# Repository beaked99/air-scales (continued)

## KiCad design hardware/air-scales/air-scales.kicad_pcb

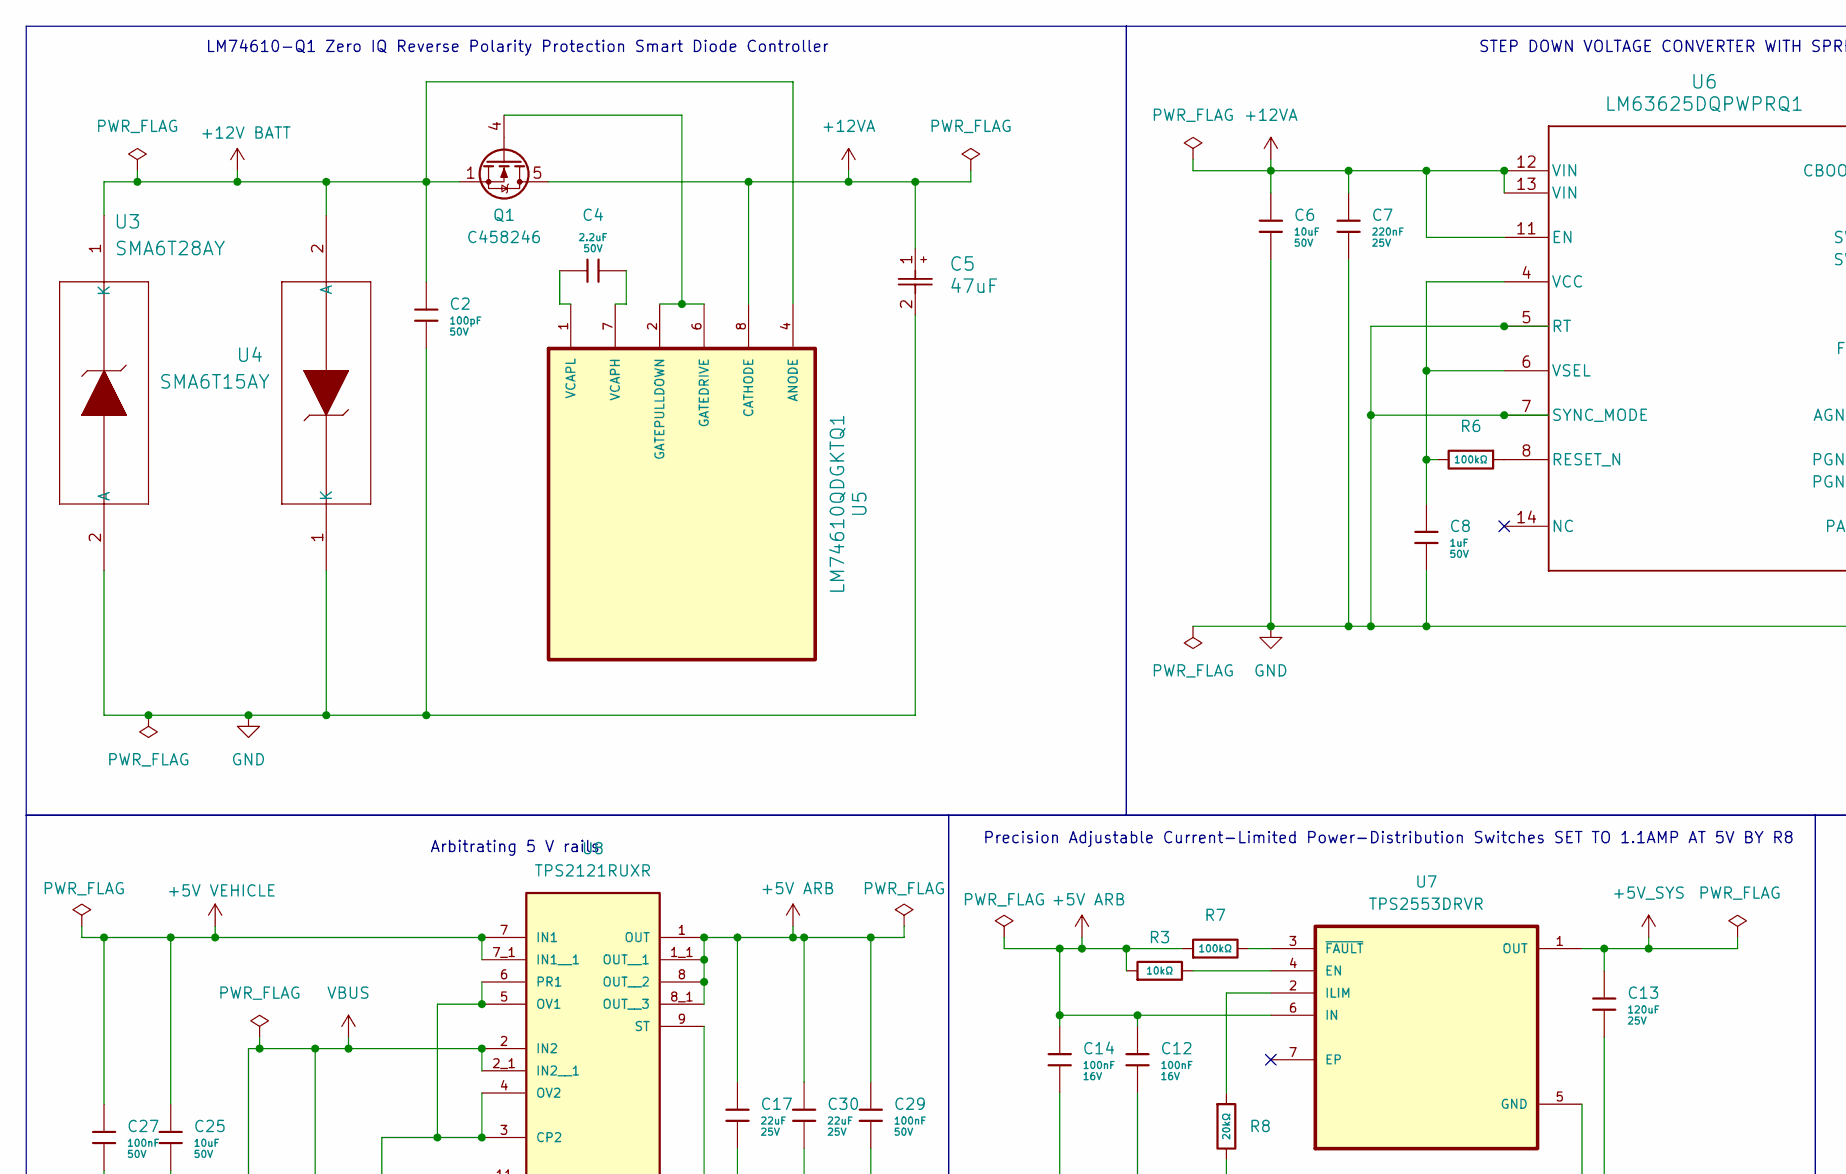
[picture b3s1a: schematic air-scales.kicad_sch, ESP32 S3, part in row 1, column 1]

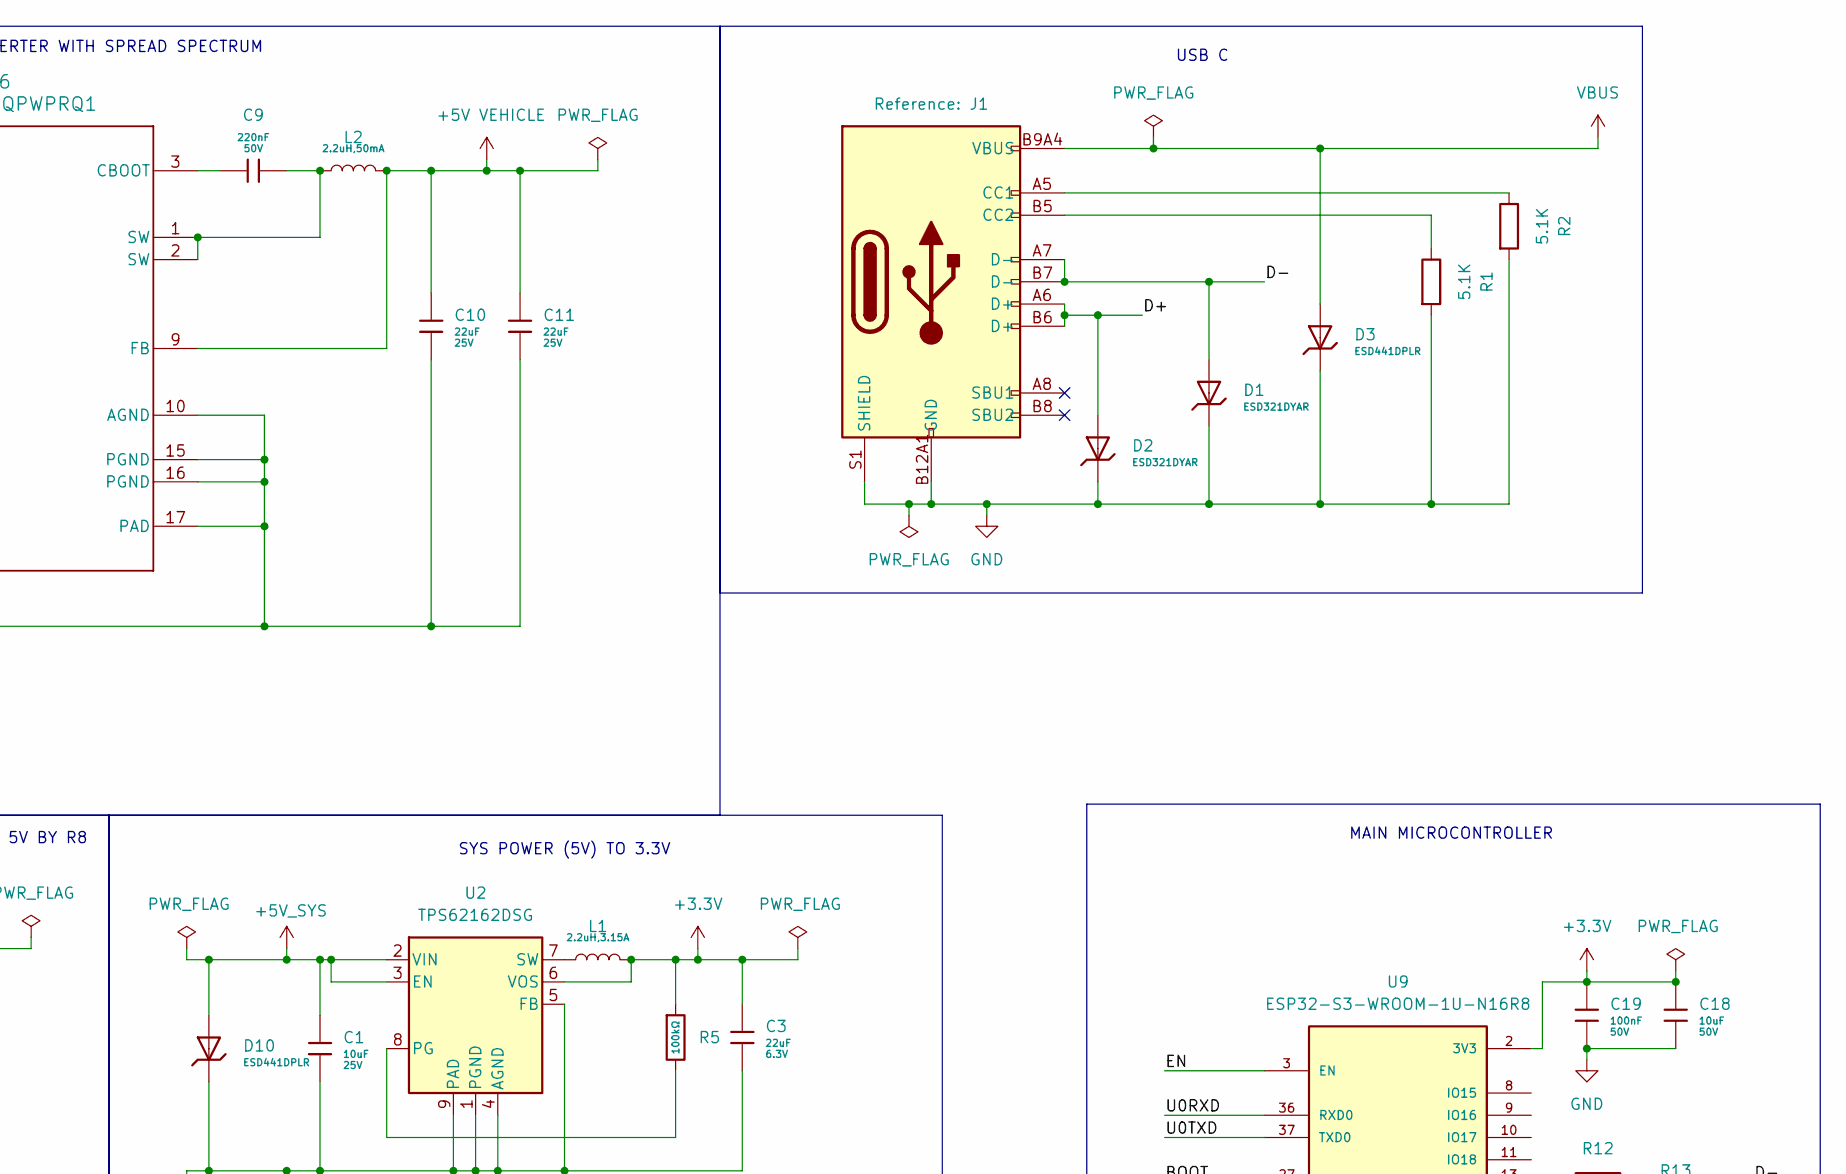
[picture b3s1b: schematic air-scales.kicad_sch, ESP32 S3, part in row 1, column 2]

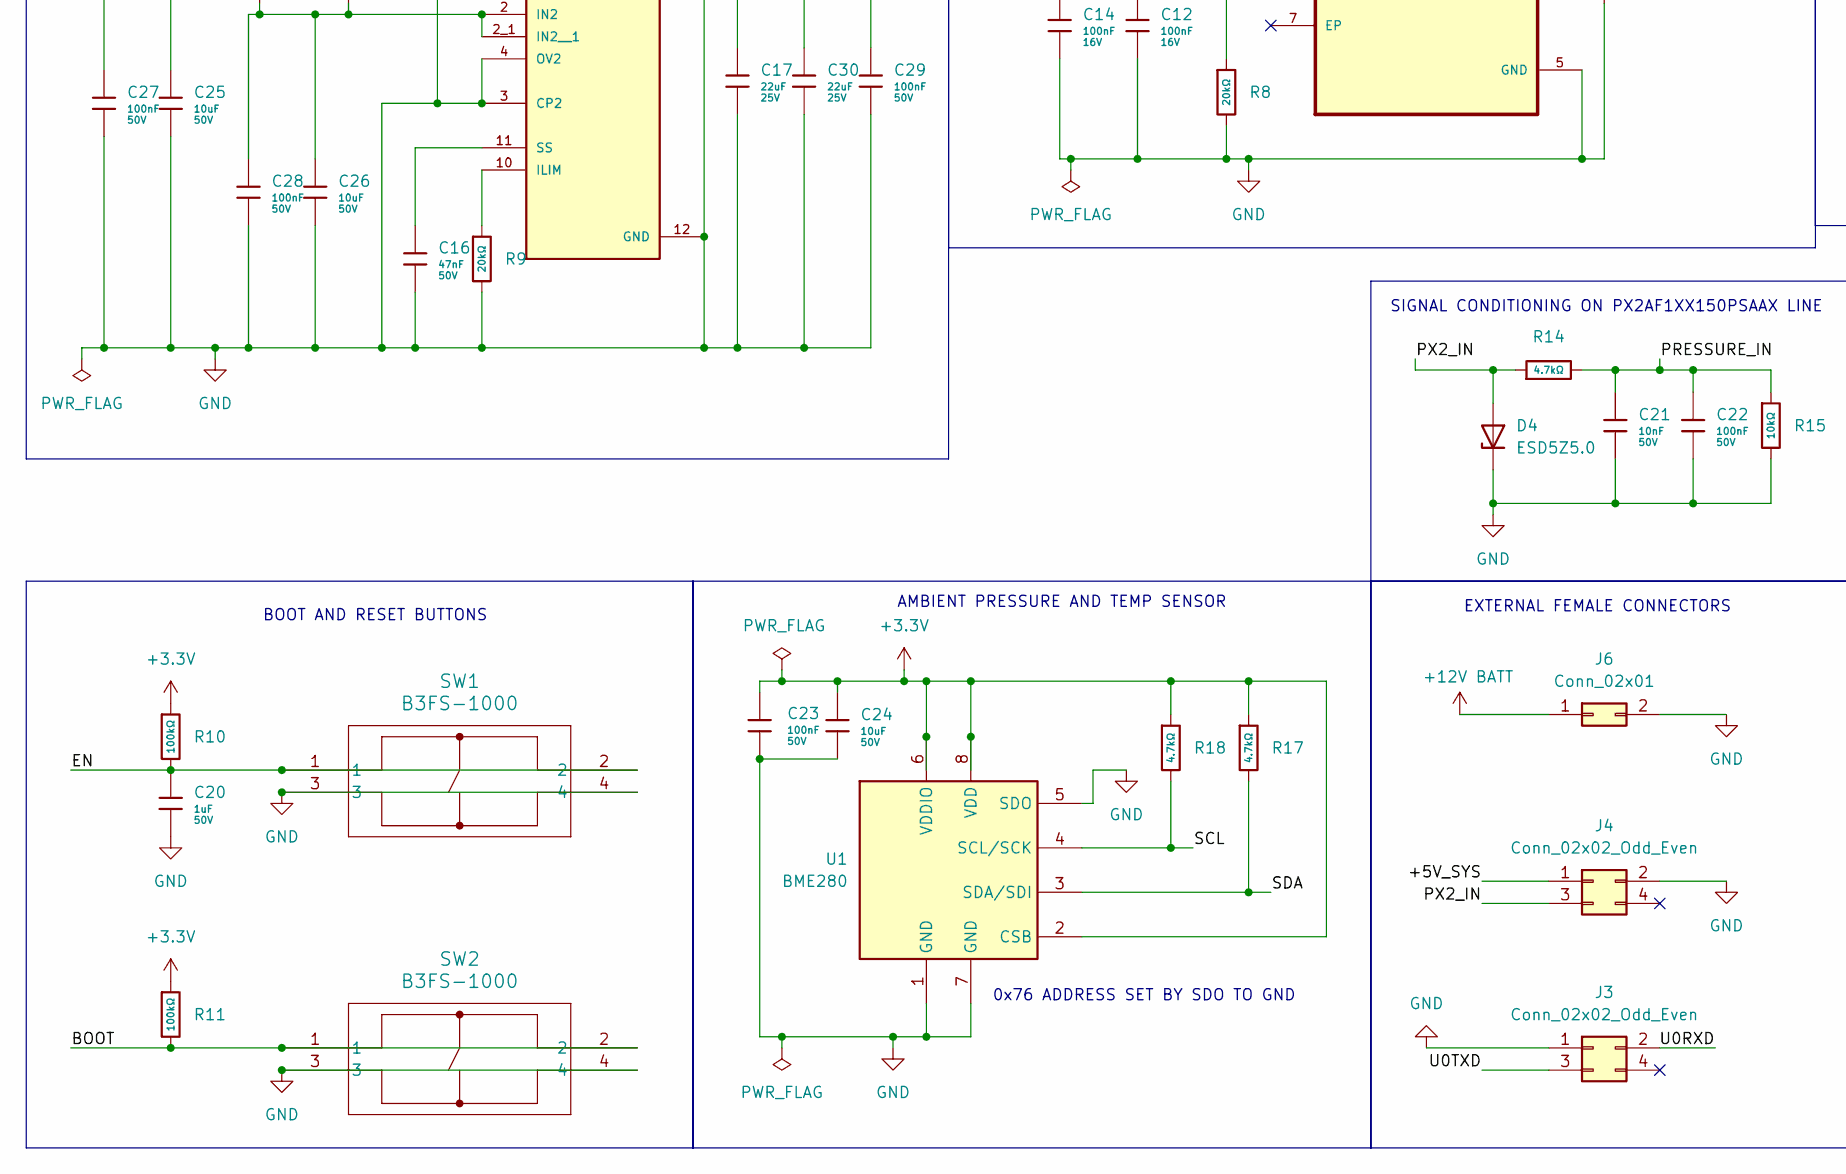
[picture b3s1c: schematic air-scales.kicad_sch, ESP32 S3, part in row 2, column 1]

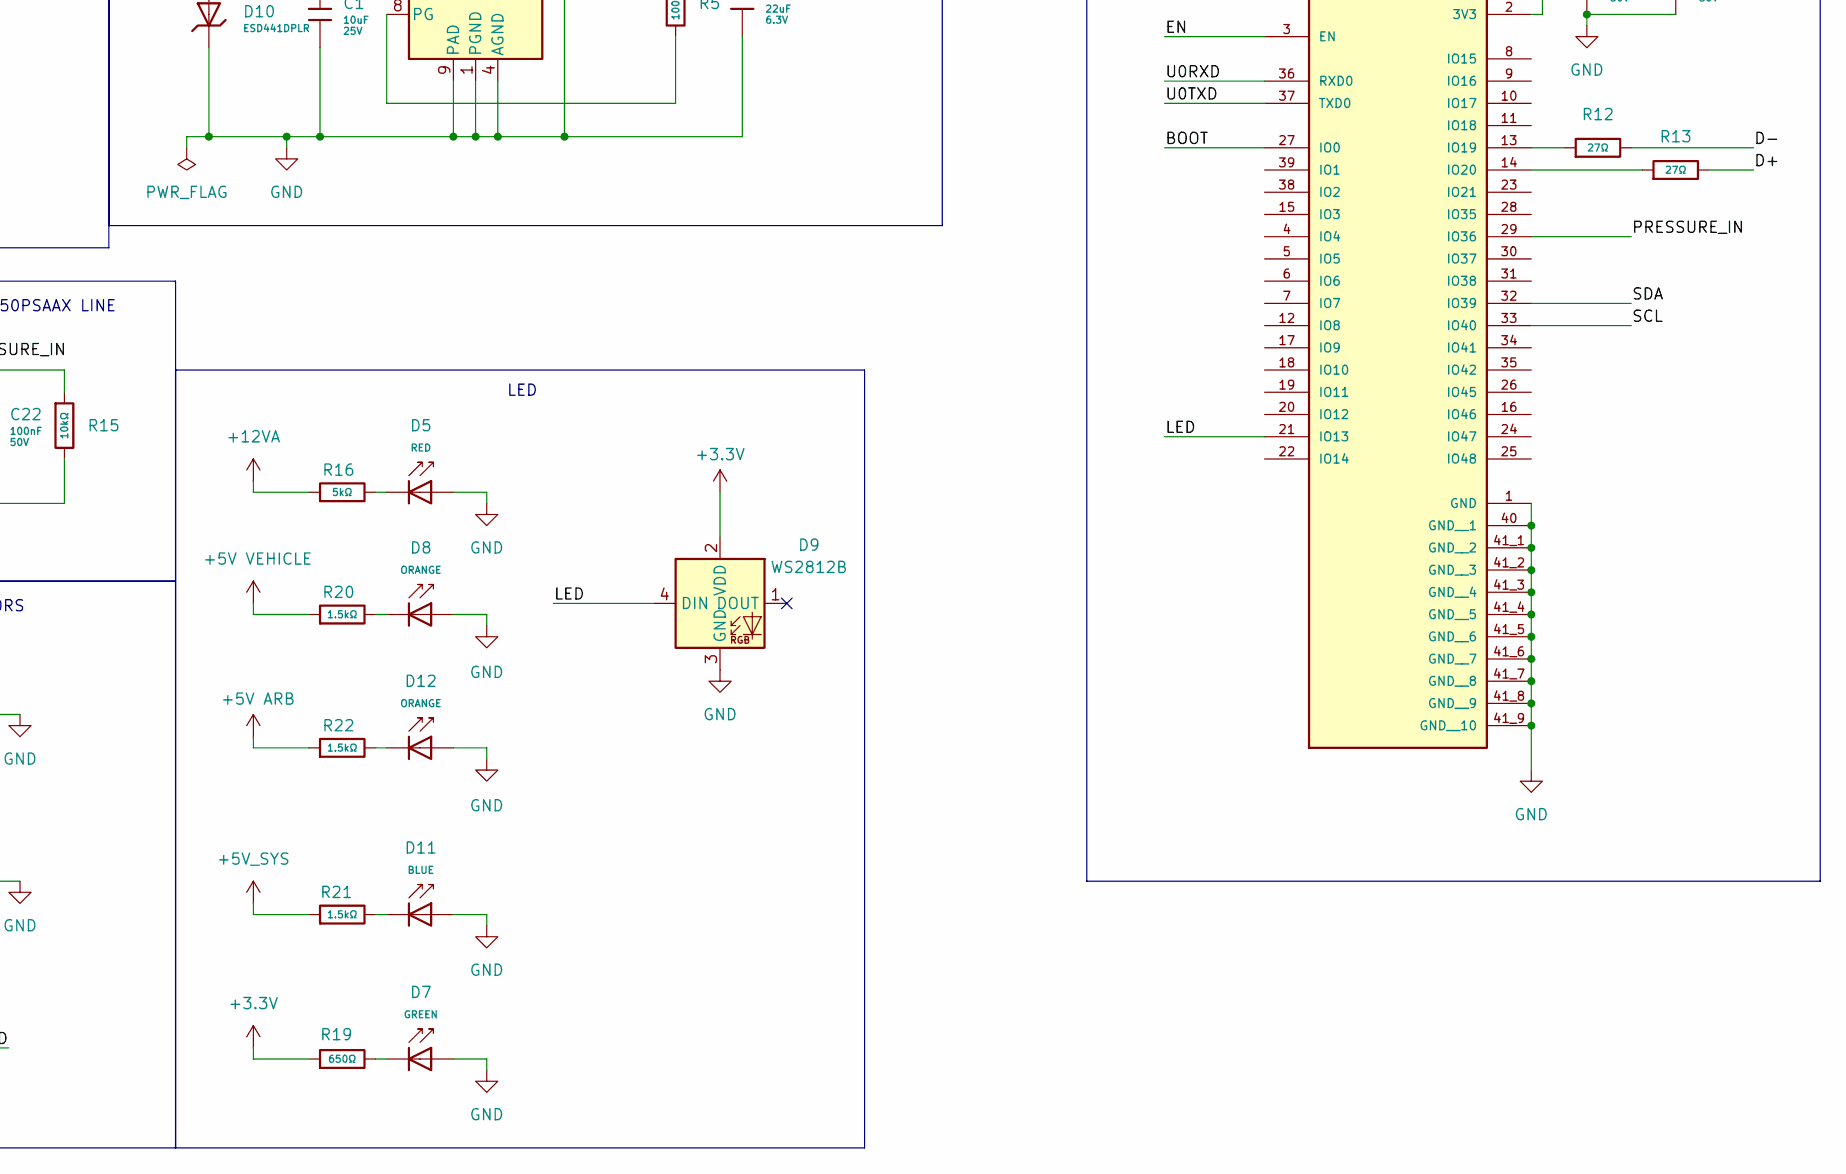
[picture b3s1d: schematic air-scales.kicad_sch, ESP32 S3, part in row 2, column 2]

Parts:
C1: 10uF; C_0603; Voltage Rated 25V; Tolerance ±20%; Part CL10A106MA8NRNC; LCSC C96446
C2: 100pF; C_0402; Voltage Rated 50V; Tolerance ±5%; Part 0402CG101J500NT; LCSC C1546
C3: 22uF; C_0603; Voltage Rated 6.3V; Tolerance ±20%; Part CL10A226MQ8NRNC; LCSC C59461
C4: 2.2uF; C_1206; Voltage Rated 50V; Tolerance ±10%; Part CL31B225KBHNNNE; LCSC C50254
C5: 47uF; CAP_PC_10X12P7_NCH
C6, C18, C24, C25, C26: 10uF; C_1206; Voltage Rated 50V; Tolerance ±10%; Part CL31A106KBHNNNE; LCSC C13585
C7: 220nF; C_0603; Voltage Rated 25V; Tolerance ±10%; Part CL10B224KA8NNNC; LCSC C21120
C8: 1uF; C_1206; Voltage Rated 50V; Tolerance ±10%; Part CL31B105KBHNNNE; LCSC C1848
C9: 220nF; C_1206; Voltage Rated 50V; Tolerance ±10%; Part 1206B224K500NT; LCSC C1857
C10, C11, C17, C30: 22uF; C_1206; Voltage Rated 25V; Tolerance ±10%; Part CL31A226KAHNNNE; LCSC C12891
C12, C14: 100nF; C_0402; Voltage Rated 16V; Tolerance ±10%; Part CL05B104KO5NNNC; LCSC C1525
C13: 120uF; C_0603; Voltage Rated 25V; Tolerance ±20%; Part CL10A106MA8NRNC; LCSC C96446
C16: 47nF; C_0603; Voltage Rated 50V; Tolerance ±10%; Part CL10B473KB8NNNC; LCSC C1622
C19, C22, C23, C27, C28, C29: 100nF; C_0603; Voltage Rated 50V; Tolerance ±10%; Part CC0603KRX7R9BB104; LCSC C14663
C20: 1uF; C_0603; Voltage Rated 50V; Tolerance ±10%; Part CL10A105KB8NNNC; LCSC C15849
C21: 10nF; C_0603; Voltage Rated 50V; Tolerance ±10%; Part 0603B103K500NT; LCSC C57112
D1, D2: ESD321DYAR; D_SOD-523; Part H5VND5BA; LCSC C42413899
D3, D10: ESD441DPLR; D_SOD-123FL; Part SMF20A; LCSC C41411782
D4: ESD5Z5.0; D_SOD-523
D5: RED; D_0603; Part KT-0603R; LCSC C2286
D7: GREEN; D_0603; Part KT-0603R; LCSC C2286
D8, D12: ORANGE; D_0603; Part KT-0603R; LCSC C2286
D9: WS2812B; LED-SMD_4P-L1.6-W1.5_XL-1615RGBC-WS2812B; LCSC C5349954
D11: BLUE; D_0603; Part KT-0603R; LCSC C2286
J1: Connector, USB-TYPE-C-16P; TYPE-C-SMD_HX-TYPE-C-16PIN; LCSC C2927039
J3, J4: Conn_02x02_Odd_Even; Molex_Micro-Fit_3.0_43045-0418_2x02-1MP_P3.00mm_Vertical
J6: Conn_02x01; Molex_Micro-Fit_3.0_43045-0218_2x01-1MP_P3.00mm_Vertical
L1: 2.2uH,3.15A; L_0805; Tolerance ±10%; Part CMI201209U2R2KT; LCSC C1043
L2: 2.2uH,50mA; L_0805; Tolerance ±10%; Part CMI201209U2R2KT; LCSC C1043
Q1: C458246; LFPAK56
R1, R2: 5.1K; R_0603
R3, R15: 10kΩ; R_0603; Overload Voltage (Max) 75V; Tolerance ±1%; Part 0603WAF1002T5E; LCSC C25804
R5, R6, R7, R10, R11: 100kΩ; R_0603; Overload Voltage (Max) 75V; Tolerance ±1%; Part 0603WAF1003T5E; LCSC C25803
R8, R9: 20kΩ; R_0402; Overload Voltage (Max) 50V; Tolerance ±1%; Part 0402WGF2002TCE; LCSC C25765
R12, R13: 27Ω; R_0603; Overload Voltage (Max) 75V; Tolerance ±1%; Part 0603WAF270JT5E; LCSC C25190
R14, R17, R18: 4.7kΩ; R_0603; Overload Voltage (Max) 75V; Tolerance ±1%; Part 0603WAF4701T5E; LCSC C23162
R16: 5kΩ; R_0603; Overload Voltage (Max) 75V; Tolerance ±1%; Part 0603WAF1002T5E
R19: 650Ω; R_0603; Overload Voltage (Max) 75V; Tolerance ±1%; Part 0603WAF3301T5E
R20, R21, R22: 1.5kΩ; R_0603; Overload Voltage (Max) 75V; Tolerance ±1%; Part 0603WAF3301T5E
SW1, SW2: B3FS-1000; SW_B3FS-1000_OMR
U1: BME280; Bosch_LGA-8_2.5x2.5mm_P0.65mm_ClockwisePinNumbering; LCSC C92489
U2: TPS62162DSG; WSON-8-1EP_2x2mm_P0.5mm_EP0.9x1.6mm_ThermalVias
U3: SMA6T28AY; SMA_UNI_STM
U4: SMA6T15AY; SMA_UNI_STM
U5: LM74610QDGKTQ1; SOP65P490X110-8N
U6: LM63625DQPWPRQ1; PWP0016K_N
U7: TPS2553DRVR; SON65P200X200X80-7N
U8: TPS2121RUXR; IC_TPS2121RUXR
U9: ESP32-S3-WROOM-1U-N16R8; XCVR_ESP32-S3-WROOM-1U-N16R8; PARTREV v1.1; LCSC C3013946

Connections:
+3.3V: C3.1, C18.1, C19.1, C23.1, C24.1, D9.2 (VDD), L1.2, R5.1, R10.1, R11.1, R17.1, R18.1, R19.1, U1.2 (CSB), U1.6 (VDDIO), U1.8 (VDD), U2.6 (VOS), U9.2 (3V3)
+5V ARB: C12.1, C14.1, C17.1, C29.1, C30.1, R3.1, R7.1, R22.1, U7.6 (IN), U8.1 (OUT), U8.1_1 (OUT__1), U8.8 (OUT__2), U8.8_1 (OUT__3)
+5V VEHICLE: C10.1, C11.1, C25.1, C27.1, L2.2, R20.1, U6.9 (FB), U8.7 (IN1), U8.7_1 (IN1__1)
+5V_SYS: C1.1, C13.1, D10.2, J4.1, R21.1, U2.2 (VIN), U2.3 (EN), U7.1 (OUT)
+12V BATT: C2.1, J6.1, Q1.1 (S), Q1.2 (S), Q1.3 (S), U3.1 (K), U4.2 (A), U5.4 (ANODE)
+12VA: C5.1, C6.1, C7.1, Q1.5 (D), R16.1, U5.8 (CATHODE), U6.11 (EN), U6.12 (VIN), U6.13 (VIN)
/BOOT: R11.2, SW2.1, SW2.2, U9.27 (IO0)
/D+: D2.2, J1.A6 (D+), J1.B6 (D+), R13.2
/D-: D1.2, J1.A7 (D-), J1.B7 (D-), R12.2
/EN: C20.1, R10.2, SW1.1, SW1.2, U9.3 (EN)
/LED: D9.4 (DIN), U9.21 (IO13)
/PRESSURE_IN: C21.1, C22.1, R14.2, R15.1, U9.29 (IO36)
/PX2_IN: D4.2 (A), J4.3, R14.1
/SCL: R18.2, U1.4 (SCL/SCK), U9.33 (IO40)
/SDA: R17.2, U1.3 (SDA/SDI), U9.32 (IO39)
/U0RXD: J3.2, U9.36 (RXD0)
/U0TXD: J3.3, U9.37 (TXD0)
GND: C1.2, C2.2, C3.2, C5.2, C6.2, C7.2, C8.2, C10.2, C11.2, C12.2, C13.2, C14.2, C16.2, C17.2, C18.2, C19.2, C20.2, C21.2, C22.2, C23.2, C24.2, C25.2, C26.2, C27.2, C28.2, C29.2, C30.2, D1.1, D2.1, D3.1, D4.1 (K), D5.2, D7.2, D8.2, D9.3 (GND), D10.1, D11.2, D12.2, J1.A12B1 (GND), J1.B12A1 (GND), J1.S1 (SHIELD), J3.1, J4.2, J6.2, R1.2, R2.2, R8.2, R9.2, R15.2, SW1.3, SW1.4, SW2.3, SW2.4, U1.1 (GND), U1.5 (SDO), U1.7 (GND), U2.1 (PGND), U2.4 (AGND), U2.5 (FB), U2.9 (PAD), U3.2 (A), U4.1 (K), U6.5 (RT), U6.7 (SYNC_MODE), U6.10 (AGND), U6.15 (PGND), U6.16 (PGND), U6.17 (PAD), U7.5 (GND), U8.3 (CP2), U8.4 (OV2), U8.5 (OV1), U8.6 (PR1), U8.9 (ST), U8.12 (GND), U9.1 (GND), U9.40 (GND__1), U9.41_1 (GND__2), U9.41_2 (GND__3), U9.41_3 (GND__4), U9.41_4 (GND__5), U9.41_5 (GND__6), U9.41_6 (GND__7), U9.41_7 (GND__8), U9.41_8 (GND__9), U9.41_9 (GND__10); also elsewhere on the board
unnamed: C9.2, L2.1, U6.1 (SW), U6.2 (SW)
unnamed: D5.1, R16.2
unnamed: D7.1, R19.2
unnamed: D8.1, R20.2
unnamed: D11.1, R21.2
unnamed: D12.1, R22.2
unnamed: J1.A5 (CC1), R2.1
unnamed: J1.B5 (CC2), R1.1
unnamed: Q1.4 (G), U5.2 (GATEPULLDOWN), U5.6 (GATEDRIVE)
unnamed: R5.2, U2.8 (PG)
unnamed: L1.1, U2.7 (SW)
unnamed: C4.2, U5.7 (VCAPH)
unnamed: C4.1, U5.1 (VCAPL)
unnamed: C9.1, U6.3 (CBOOT)
unnamed: R6.1, U6.8 (RESET_N)
unnamed: C8.1, R6.2, U6.4 (VCC), U6.6 (VSEL)
unnamed: R3.2, U7.4 (EN)
unnamed: R8.1, U7.2 (ILIM)
unnamed: R7.2, U7.3 (~FAULT)
unnamed: R9.1, U8.10 (ILIM)
unnamed: C16.1, U8.11 (SS)
unnamed: R12.1, U9.13 (IO19)
unnamed: R13.1, U9.14 (IO20)
VBUS: C26.1, C28.1, D3.2, J1.A9B4 (VBUS), J1.B9A4 (VBUS), U8.2 (IN2), U8.2_1 (IN2__1)

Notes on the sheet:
STEP DOWN VOLTAGE CONVERTER WITH SPREAD SPECTRUM
Precision Adjustable Current-Limited Power-Distribution Switches SET TO 1.1AMP AT 5V BY R8
EXTERNAL FEMALE CONNECTORS
LM74610-Q1 Zero IQ Reverse Polarity Protection Smart Diode Controller
0x76 ADDRESS SET BY SDO TO GND
Arbitrating 5 V rails
MAIN MICROCONTROLLER
SIGNAL CONDITIONING ON PX2AF1XX150PSAAX LINE
AMBIENT PRESSURE AND TEMP SENSOR
LED
USB C
BOOT AND RESET BUTTONS
SYS POWER (5V) TO 3.3V

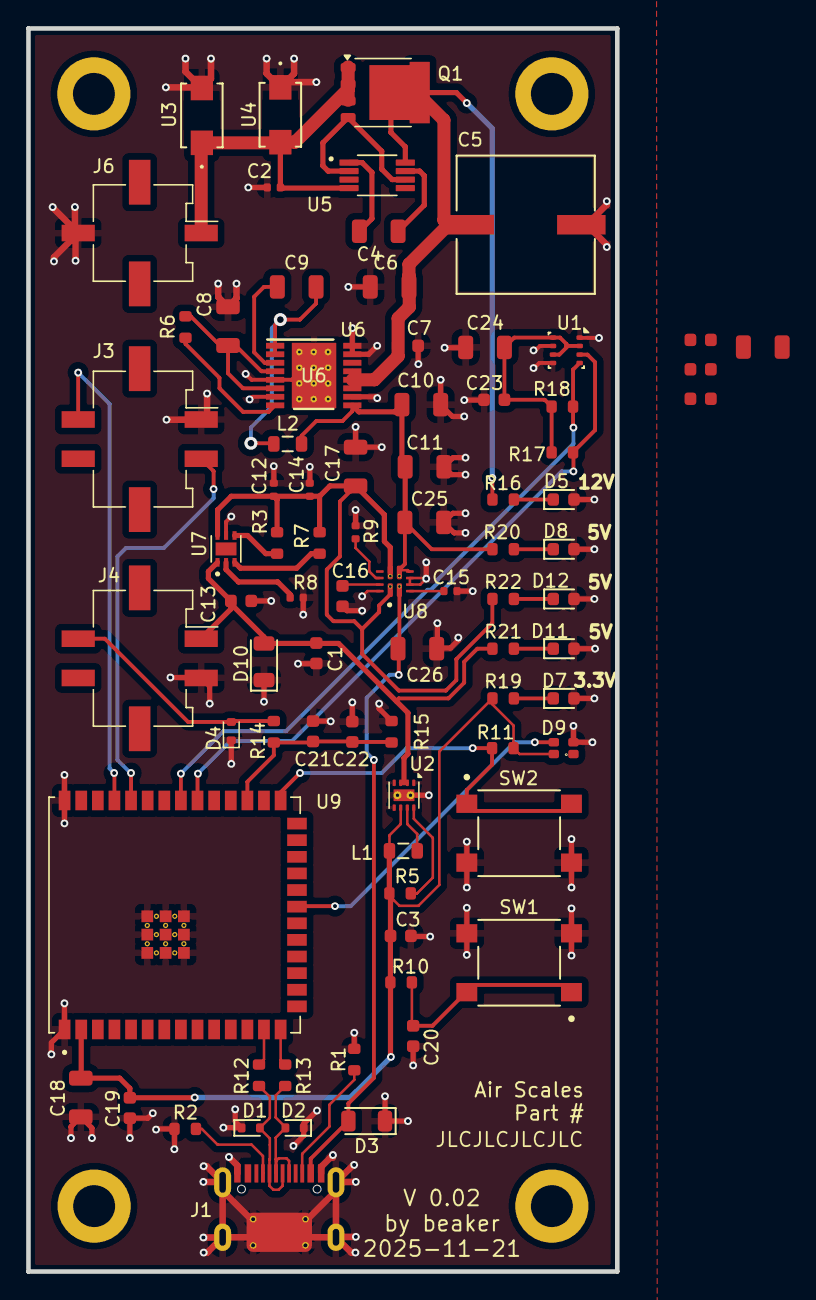
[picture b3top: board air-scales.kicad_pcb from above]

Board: 4 copper layers, 45.0 x 95.0 mm, 84 parts (0 on the bottom side), 42 nets.

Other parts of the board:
C15: 100nF; C_0402
M1, M2, M3, M4: MountingHole_3.2mm_M3_DIN965_Pad

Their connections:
GND: C15.2; also elsewhere on the board

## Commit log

2025-06-06 Add initial set of files
2025-06-06 Add webapp packages
2025-06-07 adding login page
2025-06-07 working now on admin shit
2025-06-09 admin shit for user interface now looking a lot better
2025-06-10 devices looks good so far
2025-06-10 ready for vehicle
2025-06-24 ready for vehicle again
2025-06-24 vehicles done, also added traits/timestampabletrait to src/entity.
2025-06-24 calibration complete
2025-06-24 updated calibrationcrudcontroller to properly see vehicle instead of device
2025-06-26 added a dashboard for users, links soldTo devices to their account
2025-06-26 fixed dashboard for soldTo devices now showing up as unlinked so far
2025-06-27 working on the dashboard, added configurable vehicle for devices, added axleGroup table lookup to vehicle. yeah. coming along nicely i think.
2025-06-30 dashboard calibration time
2025-06-30 dashboard calibration looking sexy af
2025-07-01 ready for digital ocean as its time to push this to the cellphone now
2025-07-01 remove sql
2025-07-01 manifest.json
2025-07-01 manifest.webmanifest
2025-07-02 microdatacontroller.php fucking time
2025-07-03 pwa time
2025-07-04 esp32 - is working, serves a page at index, has some debug shit too, websocket working
2025-07-05 wifi AP+STA now working ok - going to add BLE now b/c AP is fucked
2025-07-06 trying to get https working on the esp
2025-07-07 back to this site again to flush this out
2025-07-08 offline fallback is working gracefully
2025-07-08 offline not working
2025-07-08 working on app/index.html.twig
2025-07-08 adding shit to make js load???
2025-07-08 js is loaded - yay
2025-07-09 tailwinds and flowbite (apparently) should be working now. FUCKIN A
2025-07-09 tailwinds and flowbite (apparently) should be working now. FUCKIN A, but i gotta fix the silly package-lock.json now
2025-07-09 tailwinds depreciated to 3.7 and flowbite now working - confirmed
2025-07-09 tailwinds upgraded to v4.1.11
2025-07-09 Add @tailwindcss/postcss plugin for Tailwind v4
2025-07-12 ready to continue with development now, tw and everything else working beautifully. Great plAce to save.
2025-07-13 Fix: Sync Tailwind 3.4.17 and update styles for local + DO
2025-07-14 editing the dashboard - going smooth
2025-07-14 been tweaking the dashboard and the edit vehicle files - they look ok now
2025-07-14 calibration complete again for the 2nd time with regression working now too
2025-07-14 DO testing time
2025-07-14 fixed dashboard timestamp screwing with us
2025-07-14 here we go fucking around again
2025-07-16 i think this is a clean version and am ready to begin BLE integration ontto the ESP now
2025-07-16 BLE integration is going on up in here, v1 - no idea if this fkn works
2025-07-18 fixing dashboard sources
2025-07-18 trying to fix the damn dashboard with an updated twig.html page
2025-07-21 uploading to do
2025-07-21 uploading to do, replacing fake mock devices with real ones
2025-07-21 why am i getting 404 errors and why is bluetooth truncating to 16 digit mac addresses
2025-07-26 zip file
2025-07-26 time to fix offline mode
2025-07-26 lost a bunch of shit in the dashboard.twig.html
2025-07-27 perfect place to save. main.cpp seems to work with 2 devices, not perfectly, but good enough for now.
2025-07-28 cleaned up the calibration shit. renamed esp32apicontroller to bridgecontroller
2025-08-02 dashboard major change
2025-08-02 dashboard major change 1
2025-08-02 dashboard major change Dom time
2025-08-08 added in /device/{id} now. this looks good i think
2025-08-08 added scan for devices on dashboard cause that wasnt fucking there. totally forgot it. balls
2025-11-07 Restructure: move Symfony/PWA into webapp/
2025-11-07 moved folders around n re org shit
2025-11-07 Add hardware/ (KiCad) and update .gitignore
2025-11-07 Ignore root vendor/, var/ and webapp asset outputs
2025-11-07 Fix .gitignore: ignore root vendor/, var/, and webapp asset outputs
2025-11-07 Add hardware (KiCad) project
2025-11-07 Update .gitignore rules for hardware, vendor, var, and build outputs
2025-11-17 fixed some schematic bullshit i think, still need tvs on vbus
2025-11-20 updated all the footprints.pretty i think
2025-11-20 tvs was wrong before lm74610 so fixed that
2025-11-21 pcb placement is done round 1
2025-11-21 added pwr_flag to the power lines???
2025-11-23 need to redo a bunch of shit - lots of errors, totally fucked this all up
2025-11-28 schematic in progress
2025-12-01 PCB done????
2025-12-01 Removing files that shouldn't be in git
2025-12-01 Update gitignore to get rid of temp files
2025-12-01 Move unnecessary files removed
2025-12-01 Update schematic
2025-12-01 Tweaks to the project file
2025-12-01 time to make vias bigger and order this thing
2025-12-02 almost ready now
2025-12-02 time for bom updates
2025-12-03 ready to order the pcb
2025-12-04 order SMT025120460722-11369168A placed
2026-01-04 hardware v4 added, modified dashboard.js
2026-01-23 V0.0.9 add OTA and looks stable
